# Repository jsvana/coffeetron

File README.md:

# coffeetron - WIP

Arduino sketch to pour a shot of espresso in a [Gaggia Classic Pro](https://www.gaggia.com/manual-machines/new-classic/) to a specific weight.

Fun side project. Probably does things wrong, and isn't really useful unless you have the same setup I do. Feel free to use as a reference if you want!

## Pump control

## License

[MIT](LICENSE.md)

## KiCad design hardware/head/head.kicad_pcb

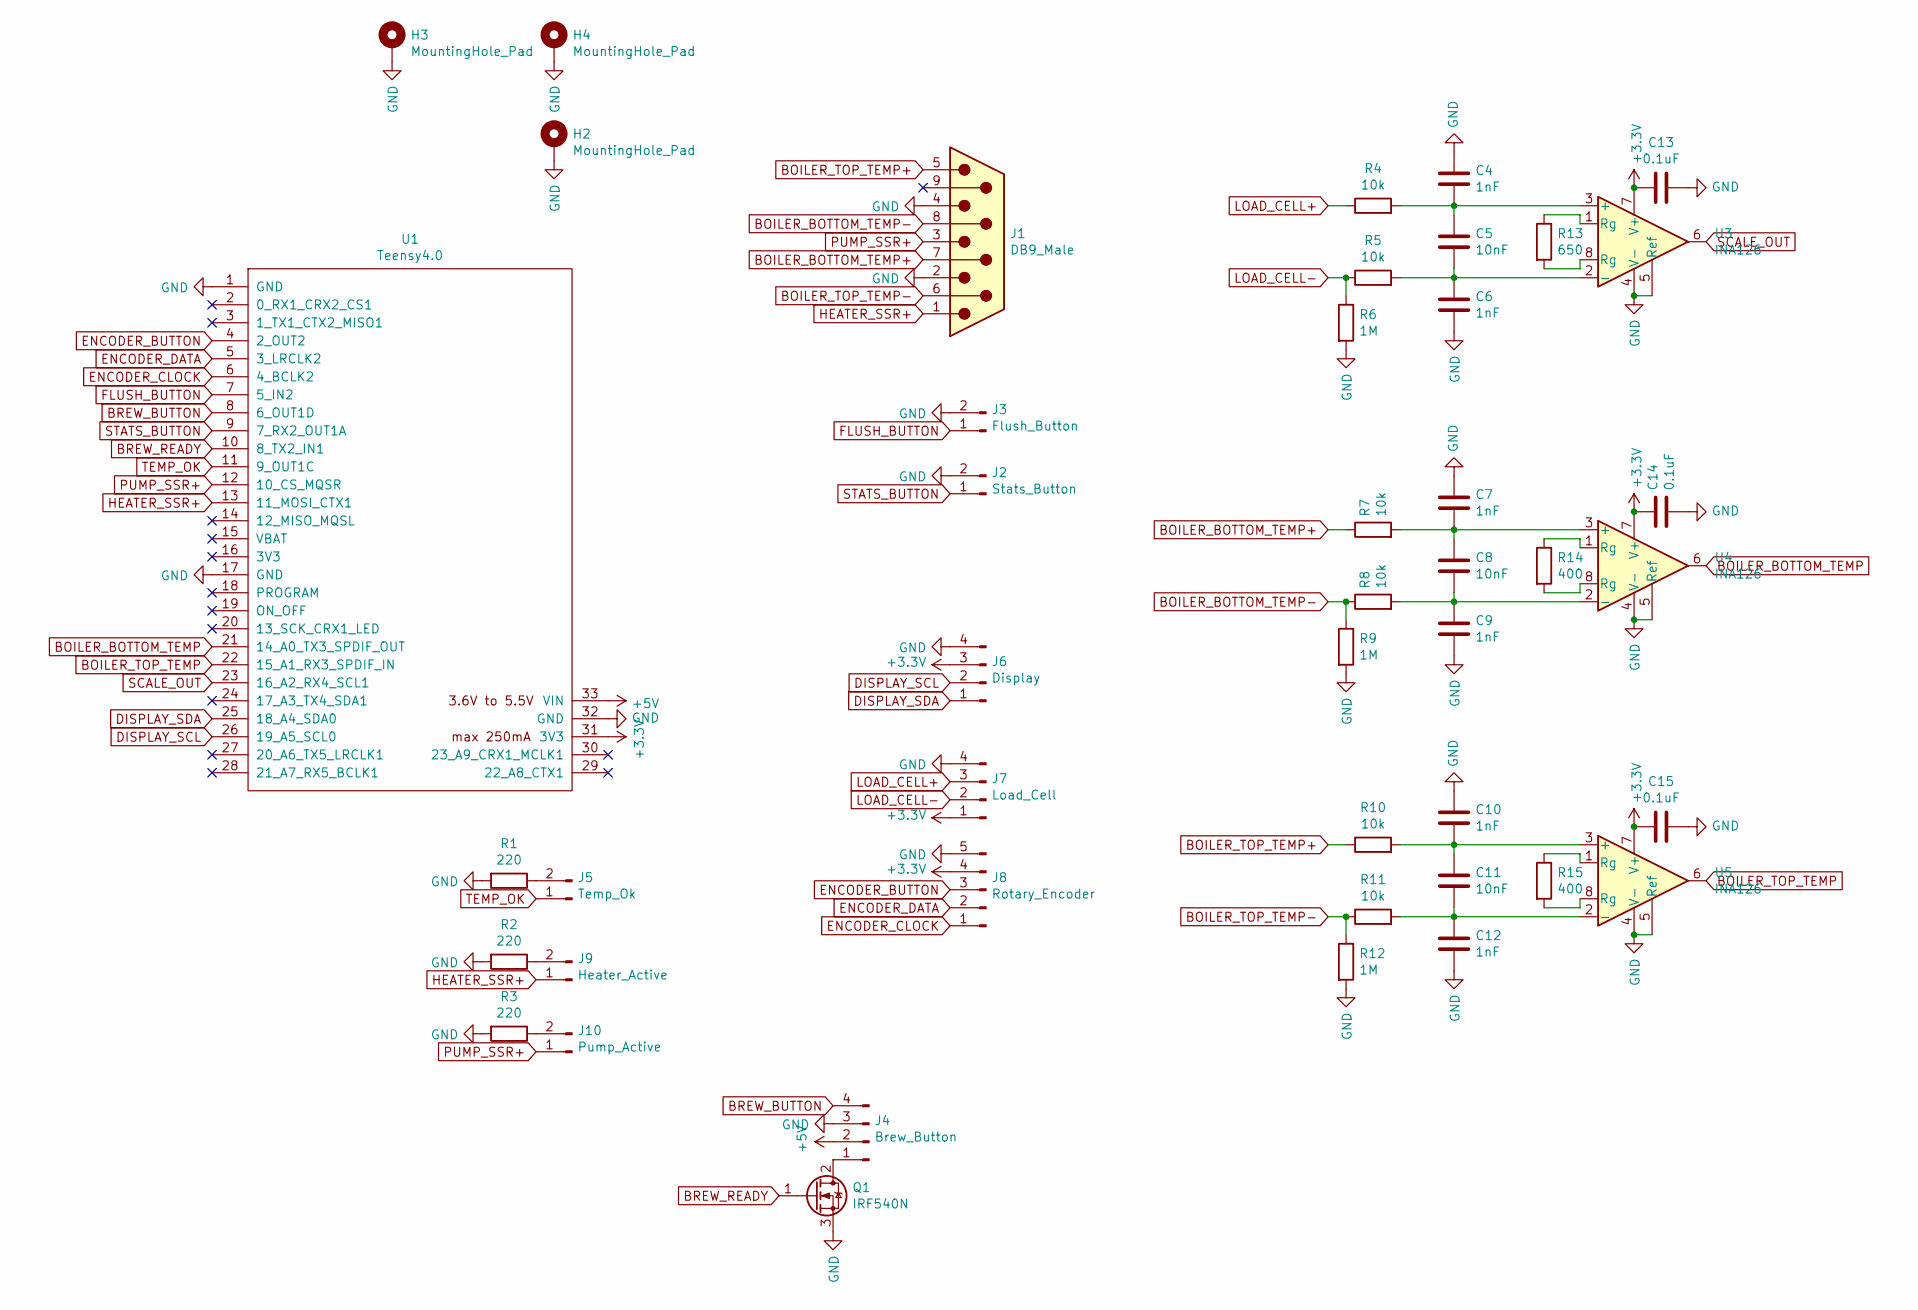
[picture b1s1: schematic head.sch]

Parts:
C4, C6, C7, C9, C10, C12: 1nF; C_Disc_D5.1mm_W3.2mm_P5.00mm
C5, C8, C11: 10nF; C_Disc_D5.1mm_W3.2mm_P5.00mm
C13, C14, C15: 0.1uF; C_Disc_D5.1mm_W3.2mm_P5.00mm
H2, H3, H4: MountingHole_Pad; MountingHole_2.5mm_Pad
J1: DB9_Male; DSUB-9_Male_Horizontal_P2.77x2.84mm_EdgePinOffset4.94mm_Hou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
J2: Stats_Button; PinHeader_1x02_P2.54mm_Vertical
J3: Flush_Button; PinHeader_1x02_P2.54mm_Vertical
J4: Brew_Button; PinHeader_1x04_P2.54mm_Vertical
J5: Temp_Ok; PinHeader_1x02_P2.54mm_Vertical
J6: Display; PinHeader_1x04_P2.54mm_Vertical
J7: Load_Cell; PinHeader_1x04_P2.54mm_Vertical
J8: Rotary_Encoder; PinHeader_1x05_P2.54mm_Vertical
J9: Heater_Active; PinHeader_1x02_P2.54mm_Vertical
J10: Pump_Active; PinHeader_1x02_P2.54mm_Vertical
Q1: IRF540N; TO-220-3_Vertical
R1, R2, R3: 220; R_Axial_DIN0204_L3.6mm_D1.6mm_P5.08mm_Horizontal
R4, R5, R7, R8, R10, R11: 10k; R_Axial_DIN0204_L3.6mm_D1.6mm_P5.08mm_Horizontal
R6, R9, R12: 1M; R_Axial_DIN0204_L3.6mm_D1.6mm_P5.08mm_Horizontal
R13: 650; R_Axial_DIN0204_L3.6mm_D1.6mm_P5.08mm_Horizontal
R14, R15: 400; R_Axial_DIN0204_L3.6mm_D1.6mm_P5.08mm_Horizontal
U1: Teensy4.0; Teensy40_SMT
U3, U4, U5: INA126; DIP-8_W7.62mm

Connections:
+3V3: C13.1, C14.1, C15.1, J6.3, J7.1, J8.4, U1.31 (3V3), U3.7 (V+), U4.7 (V+), U5.7 (V+)
+5V: J4.2, U1.33 (VIN)
BOILER_BOTTOM_TEMP: U1.21 (14_A0_TX3_SPDIF_OUT), U4.6
BOILER_BOTTOM_TEMP+: J1.7, R7.1
BOILER_BOTTOM_TEMP-: J1.8, R8.1, R9.1
BOILER_TOP_TEMP: U1.22 (15_A1_RX3_SPDIF_IN), U5.6
BOILER_TOP_TEMP+: J1.5, R10.1
BOILER_TOP_TEMP-: J1.6, R11.1, R12.1
BREW_BUTTON: J4.4, U1.8 (6_OUT1D)
BREW_READY: Q1.1 (G), U1.10 (8_TX2_IN1)
DISPLAY_SCL: J6.2, U1.26 (19_A5_SCL0)
DISPLAY_SDA: J6.1, U1.25 (18_A4_SDA0)
ENCODER_BUTTON: J8.3, U1.4 (2_OUT2)
ENCODER_CLOCK: J8.1, U1.6 (4_BCLK2)
ENCODER_DATA: J8.2, U1.5 (3_LRCLK2)
FLUSH_BUTTON: J3.1, U1.7 (5_IN2)
GND: C4.1, C6.2, C7.1, C9.2, C10.1, C12.2, C13.2, C14.2, C15.2, H2.1, H3.1, H4.1, J1.2, J1.4, J2.2, J3.2, J4.3, J6.4, J7.4, J8.5, Q1.3 (S), R1.2, R2.2, R3.2, R6.2, R9.2, R12.2, U1.1 (GND), U1.17 (GND), U1.32 (GND), U3.4 (V-), U3.5 (Ref), U4.4 (V-), U4.5 (Ref), U5.4 (V-), U5.5 (Ref)
HEATER_SSR+: J1.1, J9.1, U1.13 (11_MOSI_CTX1)
LOAD_CELL+: J7.3, R4.1
LOAD_CELL-: J7.2, R5.1, R6.1
unnamed: C4.2, C5.1, R4.2, U3.3 (+)
unnamed: C5.2, C6.1, R5.2, U3.2 (-)
unnamed: C7.2, C8.1, R7.2, U4.3 (+)
unnamed: C8.2, C9.1, R8.2, U4.2 (-)
unnamed: C10.2, C11.1, R10.2, U5.3 (+)
unnamed: C11.2, C12.1, R11.2, U5.2 (-)
unnamed: J4.1, Q1.2 (D)
unnamed: J5.2, R1.1
unnamed: J9.2, R2.1
unnamed: J10.2, R3.1
unnamed: R13.1, U3.1 (Rg)
unnamed: R13.2, U3.8 (Rg)
unnamed: R14.1, U4.1 (Rg)
unnamed: R14.2, U4.8 (Rg)
unnamed: R15.1, U5.1 (Rg)
unnamed: R15.2, U5.8 (Rg)
PUMP_SSR+: J1.3, J10.1, U1.12 (10_CS_MQSR)
SCALE_OUT: U1.23 (16_A2_RX4_SCL1), U3.6
STATS_BUTTON: J2.1, U1.9 (7_RX2_OUT1A)
TEMP_OK: J5.1, U1.11 (9_OUT1C)

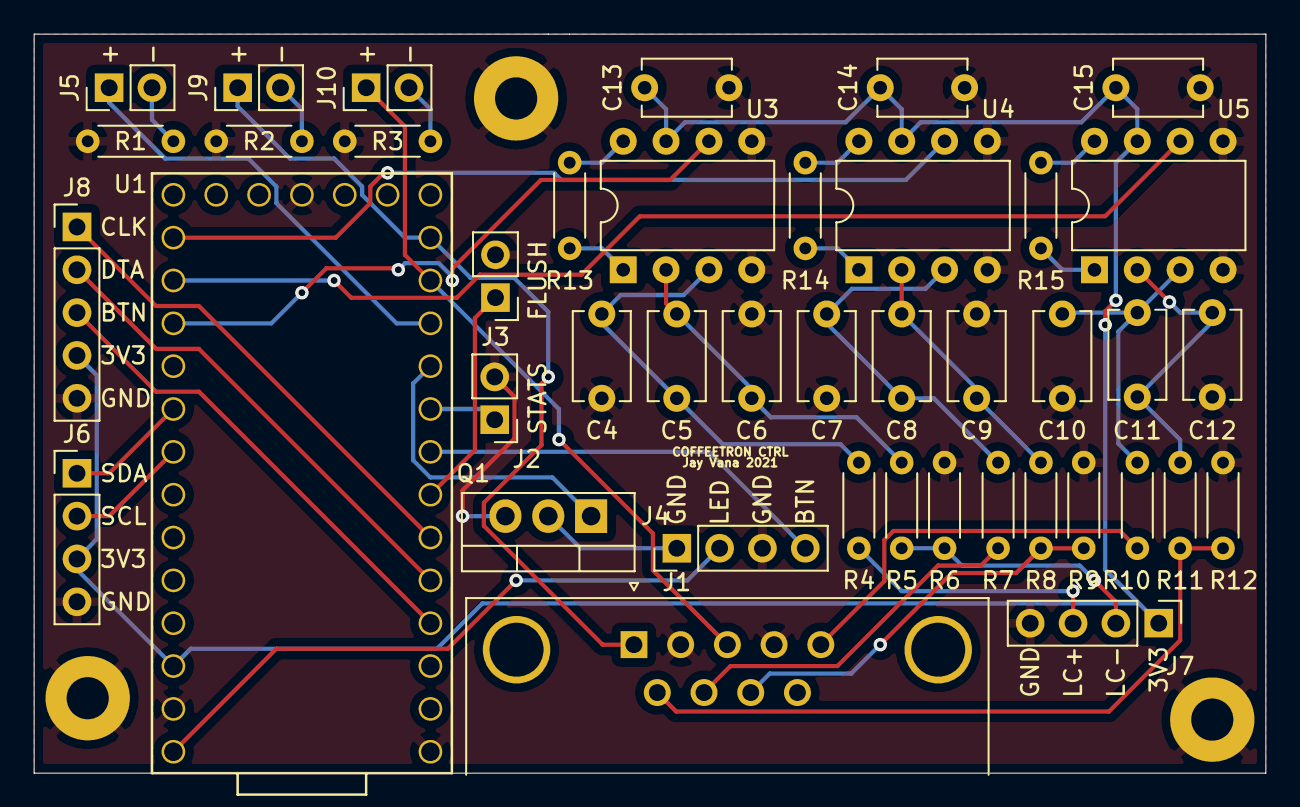
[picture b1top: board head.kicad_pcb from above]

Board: 2 copper layers, 73.0 x 43.8 mm, 45 parts (0 on the bottom side), 40 nets.

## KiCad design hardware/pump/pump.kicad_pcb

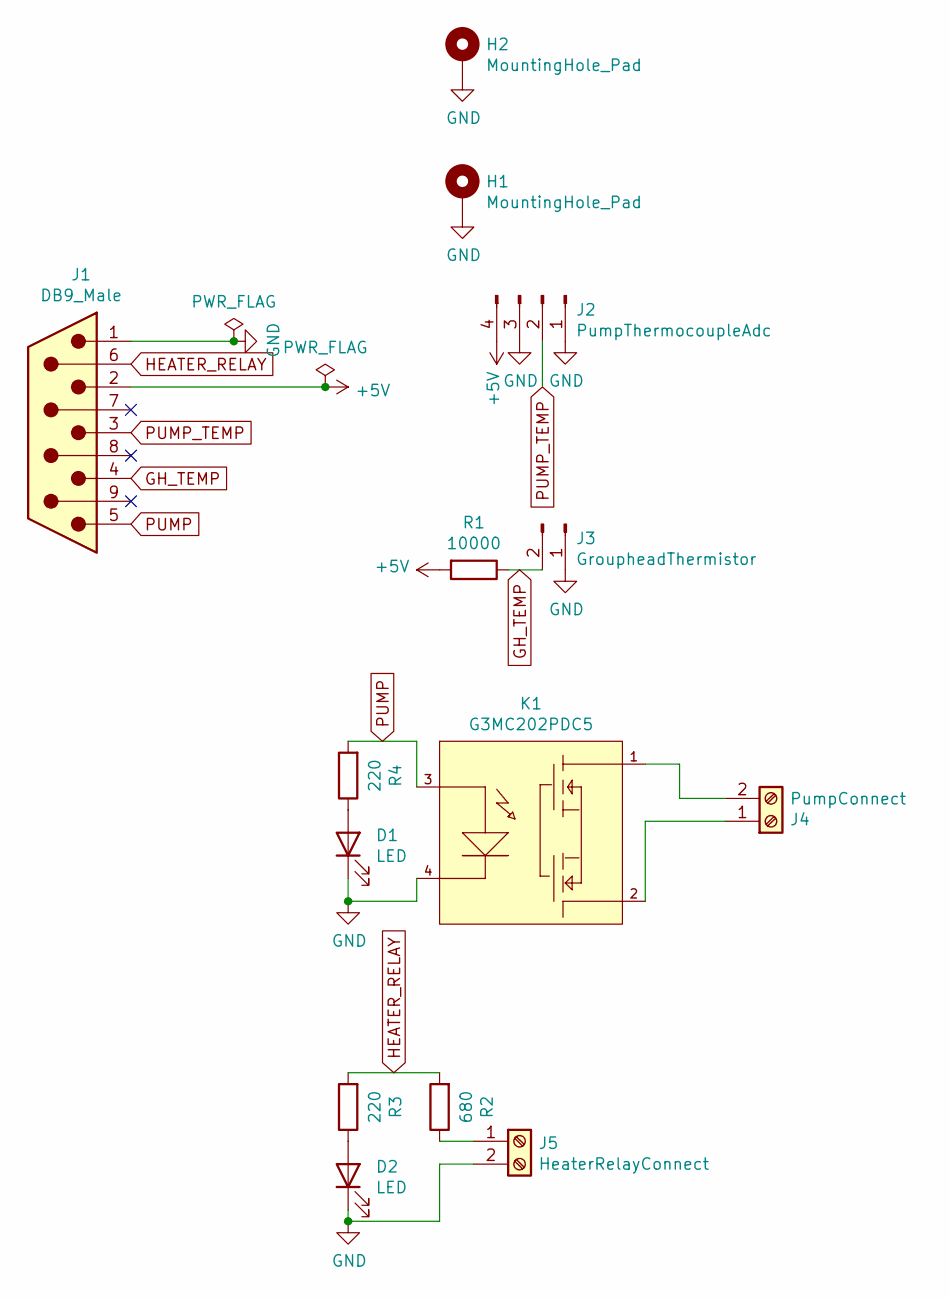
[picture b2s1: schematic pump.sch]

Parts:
D1, D2: LED; LED_D3.0mm
H1, H2: MountingHole_Pad; MountingHole_4.3mm_M4_Pad
J1: DB9_Male; DSUB-9_Male_Horizontal_P2.77x2.84mm_EdgePinOffset4.94mm_Hou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
J2: PumpThermocoupleAdc; PinHeader_1x04_P2.54mm_Vertical
J3: GroupheadThermistor; PinHeader_1x02_P2.54mm_Vertical
J4: PumpConnect; TerminalBlock_Phoenix_MKDS-1,5-2-5.08_1x02_P5.08mm_Horizont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
J5: HeaterRelayConnect; TerminalBlock_Phoenix_MKDS-1,5-2-5.08_1x02_P5.08mm_Horizont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
K1: G3MC202PDC5; Omron-G3MC202PDC5-0-0-0; output voltage 1.6V; voltage rating AC 100-240V; mouser part number 653-G3MC-202P-DC5; digikey description RELAY SSR SPST-NO SIP 5VDC
R1: 10000; R_Axial_DIN0204_L3.6mm_D1.6mm_P7.62mm_Horizontal
R2: 680; R_Axial_DIN0204_L3.6mm_D1.6mm_P7.62mm_Horizontal
R3, R4: 220; R_Axial_DIN0204_L3.6mm_D1.6mm_P7.62mm_Horizontal

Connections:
+5V: J1.2, J2.4, R1.2
GH_TEMP: J1.4, J3.2, R1.1
GND: D1.1 (K), D2.1 (K), H1.1, H2.1, J1.1, J2.1, J2.3, J3.1, J5.2, K1.4 (-)
HEATER_RELAY: J1.6, R2.2, R3.2
unnamed: D1.2 (A), R4.1
unnamed: D2.2 (A), R3.1
unnamed: J4.1, K1.2
unnamed: J4.2, K1.1
unnamed: J5.1, R2.1
PUMP: J1.5, K1.3 (+), R4.2
PUMP_TEMP: J1.3, J2.2

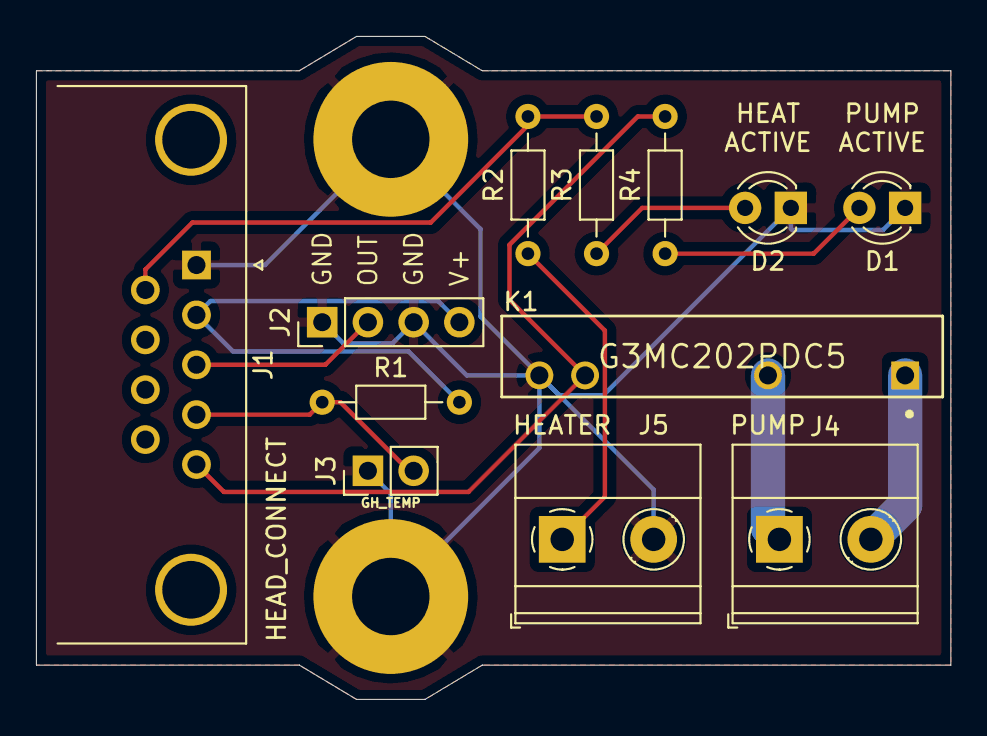
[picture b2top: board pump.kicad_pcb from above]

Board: 2 copper layers, 50.8 x 36.8 mm, 14 parts (0 on the bottom side), 11 nets.

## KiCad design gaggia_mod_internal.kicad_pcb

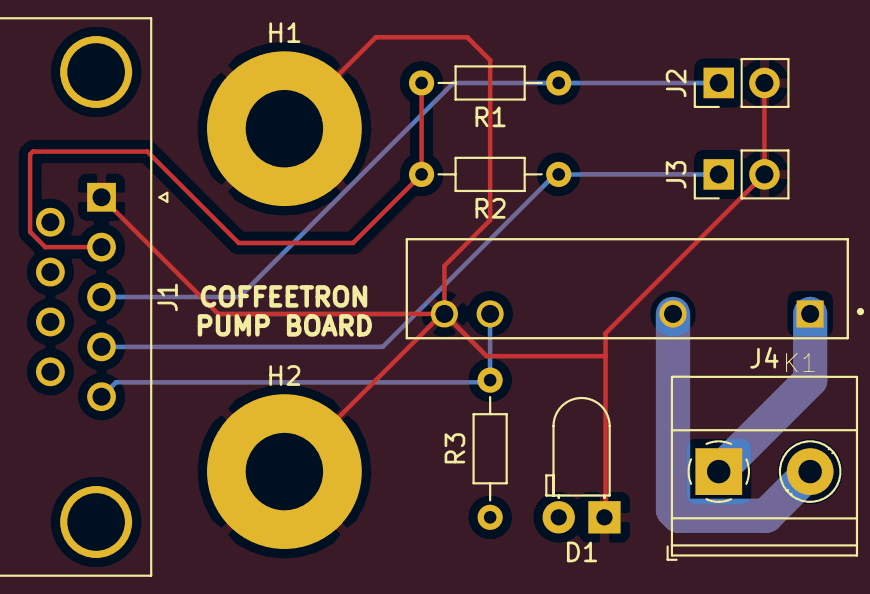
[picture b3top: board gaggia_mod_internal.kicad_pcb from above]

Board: 2 copper layers, 11 parts (0 on the bottom side), 8 nets.

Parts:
D1: LED; LED_D3.0mm_Horizontal_O1.27mm_Z2.0mm
H1, H2: MountingHole_Pad; MountingHole_4.3mm_M4_Pad
J1: DB9_Male; DSUB-9_Male_Horizontal_P2.77x2.84mm_EdgePinOffset4.94mm_Hou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
J2: Grouphead; PinHeader_1x02_P2.54mm_Vertical
J3: Pump; PinHeader_1x02_P2.54mm_Vertical
J4: PumpConnect; TerminalBlock_Phoenix_MKDS-1,5-2-5.08_1x02_P5.08mm_Horizont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
K1: G3MC202PDC24; RELAY_G3MB202PDC12
R1, R2: 10000; R_Axial_DIN0204_L3.6mm_D1.6mm_P7.62mm_Horizontal
R3: 220; R_Axial_DIN0204_L3.6mm_D1.6mm_P7.62mm_Horizontal

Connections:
GND: D1.1, H1.1, H2.1, J1.1, J2.2, J3.2, K1.4
unnamed: D1.2, R3.1
unnamed: J1.2, R1.2, R2.2
unnamed: J1.3, J2.1, R1.1
unnamed: J1.4, J3.1, R2.1
unnamed: J1.5, K1.3, R3.2
unnamed: J4.1, K1.1
unnamed: J4.2, K1.2

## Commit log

2021-03-01 Add schematic for pump control unit
    Adds schematic for the pump control unit. This will attach to a head unit via DB9, and the head unit hasn't yet been designed.
2021-03-01 Add images
    Add images from the project
2021-03-02 State machine
2021-03-02 Preinfusion
2021-03-02 Add flush
2021-03-02 Read all values in batches
2021-03-02 Increase preinfuse pump time, clear display at start, fix temp probe
2021-03-03 Add rotary encoder
2021-03-03 Add busted encoder interrupt code
2021-03-04 [BROKEN] refactor into function pointers
2021-03-04 Make bools bools
2021-03-04 Split main file up
2021-03-04 Fix bad state transition
2021-03-04 Make rotary encoder work and buttons work better
2021-03-04 Configure weight
2021-03-04 Configurable preinfusion
2021-03-04 Allow preinfusion to be disabled
2021-03-04 Clamp inputs
2021-03-05 Add makefile and brew stats button
2021-03-05 Add TODO
2021-03-06 Finish pump design
2021-03-06 Move software into folder
2021-03-06 Update TODO
2021-03-07 Move makefile
2021-03-08 Add config for desired temperature
2021-03-08 PID control temp
2021-03-08 Remove serial write
2021-03-08 Rework pump hardware based on experimentation
2021-03-09 [BROKEN]
2021-03-09 Dedup a bit
2021-03-09 Reduce RAM util
2021-03-09 More stats
2021-03-09 Add more stats and graph data
2021-03-09 Fix removed states
2021-03-10 Graph events better
2021-03-11 Better graphing
2021-03-12 Statsssss
2021-03-15 fixes
2021-03-15 Switch to Teensy 4.0, move to Platformio
2021-03-15 Fix JSON output
2021-03-15 Use library to serialize JSON
2021-03-16 Add head unit
2021-03-18 Add gerber files
2021-03-18 Flip
2021-03-18 Fix LED label
2021-03-18 Add label, adjust ground plane
2021-03-18 Fix ground plane
2021-04-07 Update head unit
2021-04-07 Move inductor
2021-04-07 Reorder caps and resistors
2021-04-09 Vias for days
2021-04-10 Move silkscreen around
2021-04-13 Remove unnecessary boost converter
